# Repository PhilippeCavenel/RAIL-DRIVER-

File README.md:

# RAIL-DRIVER-
 Model railroad board and firmware based on PIC18F4585 

For Board Layout

Important points to remember
---------------------------

Step one: 
----------------

- Generate schematic and validate circuit with ERC
- Pay particular attention to net class, especially for the power section

Second step : 
----------------

- Component placement and automatic routing. 
- To fill in the top and bottom layers, you need to draw a polygon all around the board, selecting the right layer (Top or Bottom) in the top left-hand corner after routing (otherwise it won't work), then restart routing.
- Validate with a DRC, selecting only the Top, Bottom, Via and Pad layers.
- Finalization of the silkscreen (layer 21) by placing all indications correctly and then generating the legend for the drills on layer 144 using drillegend-stack.ulp

Step three: 
-----------------

- Generate the files for manufacturing with the CAM Processor by clicking on the CAM_JOB/RailDriverCamJob.cam file.
- In the top-left File menu, select the .brd file for the corresponding design. 
- The directories and file names must be correct in the various tabs (check and correct if necessary). 
- All that's left to do is to run PROCESS JOB to produce the files.

Fourth step: 
-----------------

- To modify the selection of unknown casings, modify the 3D_RENDERING/eagle3d/ulp/3dusrpac.dat file.  
- Update the configuration files directory in 3dconf.dat 
- Generate a 3D rendering of the design by launching the ULP icon in the layout screen 3D_RENDERING/eagle3d/ulp/3d50.ulp 
- Specify the .brd file, which will generate a .pov file that can be processed by povray to obtain the 3D rendering. 
- Select "User-defined model" in the General tab 
- Add layer 25 in Miscellaneous Case Design
- Modify Writing on plate to display layers 21 and 25 only. 
- Add layers 25 and 27 in Case Reference 
- Click on Create POVRay file and Exit. 
- Copy the generated EAGLE_FILES/RailDriver/RailDriver.pov file into 3D_RENDERING/eagle3d/povray
- Repeat the same operation, moving the camera to shoot from below (using Y) and/or from the other sides (using X and Z).
- Click on the 3D_RENDERING/eagle3d/povray/RailDriver.pov file to start building the 3D view with povray. Use 800 x 600 AA 0.3 for a reasonable image creation time, or 1600 x 1200 A 0.3 for a better resolution, but the image creation time will take several tens of minutes.
- In eagle, make a screen copy of the different layers built during the construction of the manufacturing files. Place all views in PNGVIEW.

HOW TO ADD A 3D MODEL : 
------------------------------

- Retrieve the model in stl format from the Internet (e.g. snapeda). If the model is in step format, it must first be converted to stp, for example on https://polyd.com/fr/convertir-step-en-stl-en-ligne
- Use the stl2pov.exe utility available in utilities (eagle installation directory) (launch a Windows shell) stl2pov.exe myModel.stl > myModel.inc. Copy it to 3D_RENDERING/eagle3d/povray. 

For example: stl2pov.exe "TO220HeatSink\TO220_Heatsink.stp" > "TO220HeatSink\TO220HeatSink.inc".
G
- Modify the myModel.inc file so that it is understood by povray, taking as an example: fk_222_sa.inc
- Add the following include to the 3D_RENDERING/eagle3d/povray/e3d_user.inc file: #include "myModel.inc". 
- Add the following information to the 3D_RENDERING/eagle3d/ulp/3dusrpac.dat file:

Par exemple : FK222:0:1:0:0:0:0:0:0:0:0:0:0:0:0:0:0:0:0:0:0:0:0:0:0:0:0:0:0:0:0:HEATSINK_FK_222(:HEATSINK_FK_222_GRND

Index meaning

[00] Eagle component package name
[01] Output name
[02] Output value
[03] Define color bands
[04] SMD offset (parts will be moved pcb_cuhight up/down)
[05] LED options (The LED options dialog will be displayed)
[06] Ready for sockets (see explanation)
[07] Quartz height request
[08] Has part a macro (for example, SMD jumpers)
[09] SMD resistor, Generate number combination
[10] Socket macro
[11] Height of socket in 1/10mm
[12] Comments concerning socket
[13] Internal for administration purpose (not used at present)
[14] Y axis rotation correction
[15] Correction offset x
[16] Offset correction y
[17] Correction offset z
[18] Use Prefix from Part?
[19] Shunt on pinheader (a dialog will be displayed)
[20] Logo selection dialog will be shown
[21] Reserved[8]
[29] Bounding-Box Minimum
[30] Bounding-Box Maximum
[31] POV-Ray macro (Name of pov macro and a left parenthesis)
[32] Package comments (German)
[33] Package comments (English)

Fifth stage: 
-----------------

- Update the BOM to purchase components

Sixth step:
---------------

-Compress CAM_JOB and PNGVIEW directory to start manufacturing at AllPcb: https://www.allpcb.com/ 

For Firmware : Please read documentation

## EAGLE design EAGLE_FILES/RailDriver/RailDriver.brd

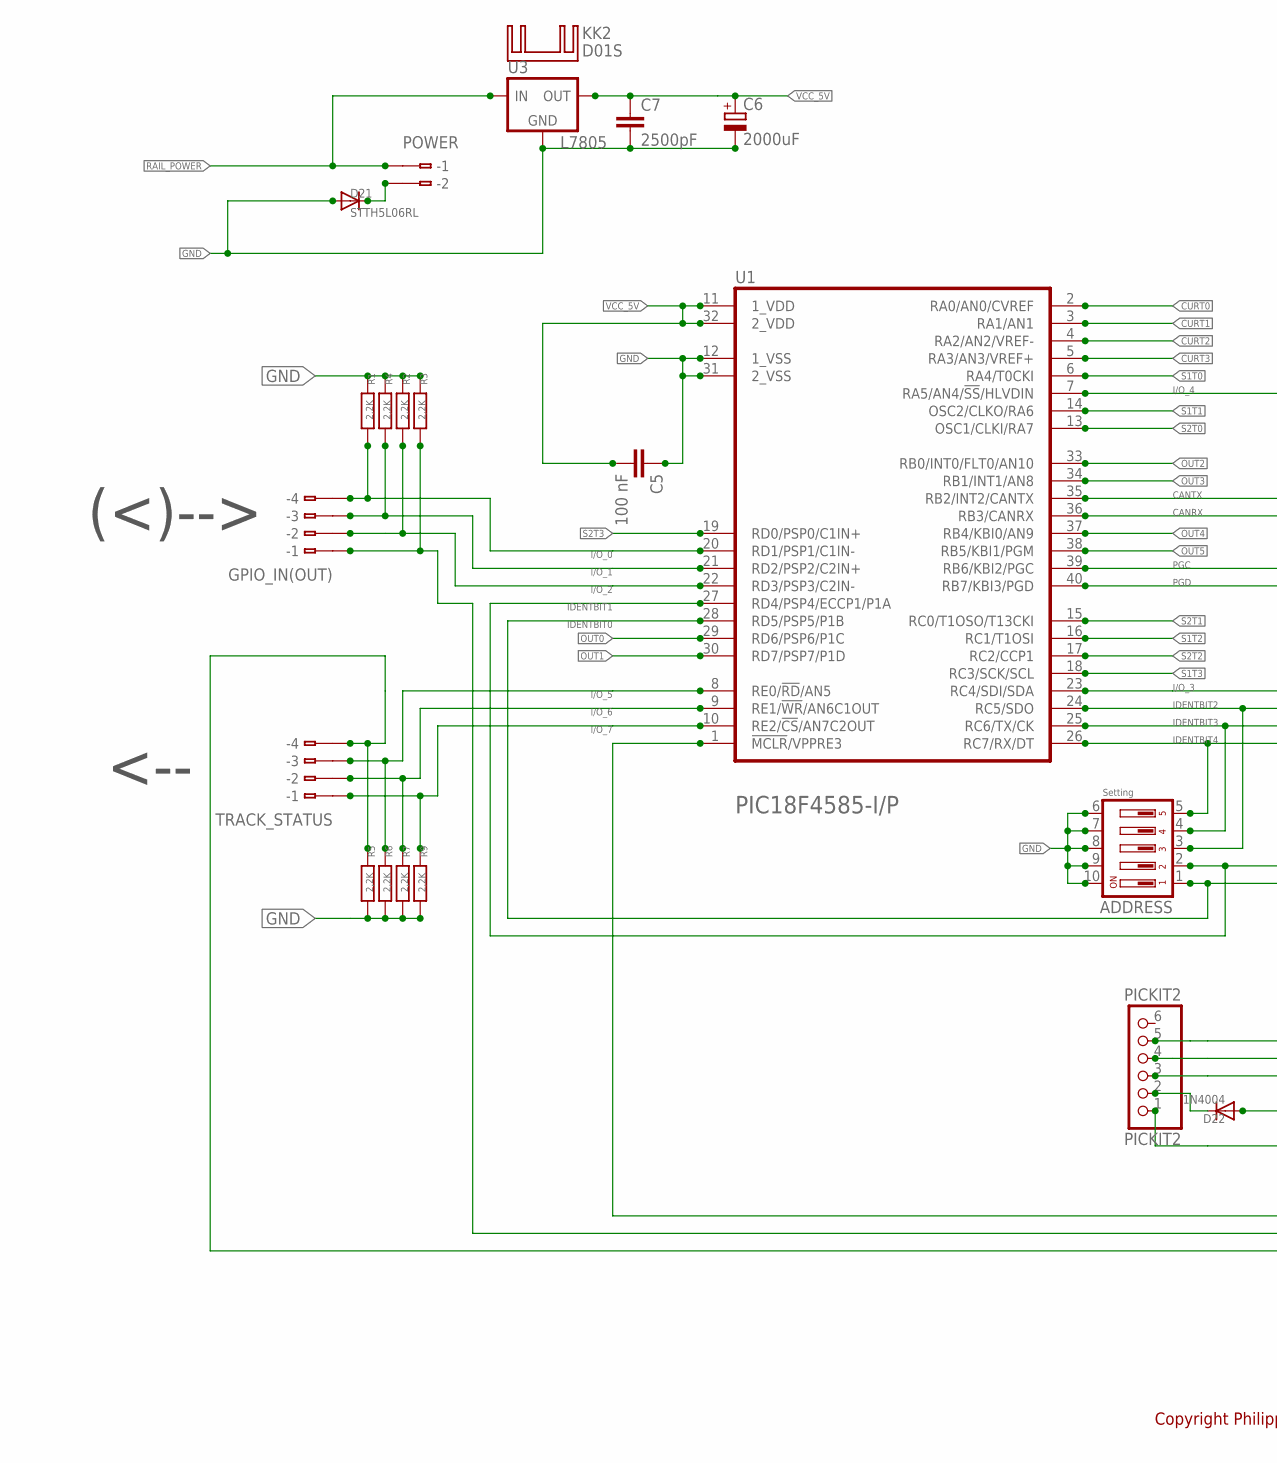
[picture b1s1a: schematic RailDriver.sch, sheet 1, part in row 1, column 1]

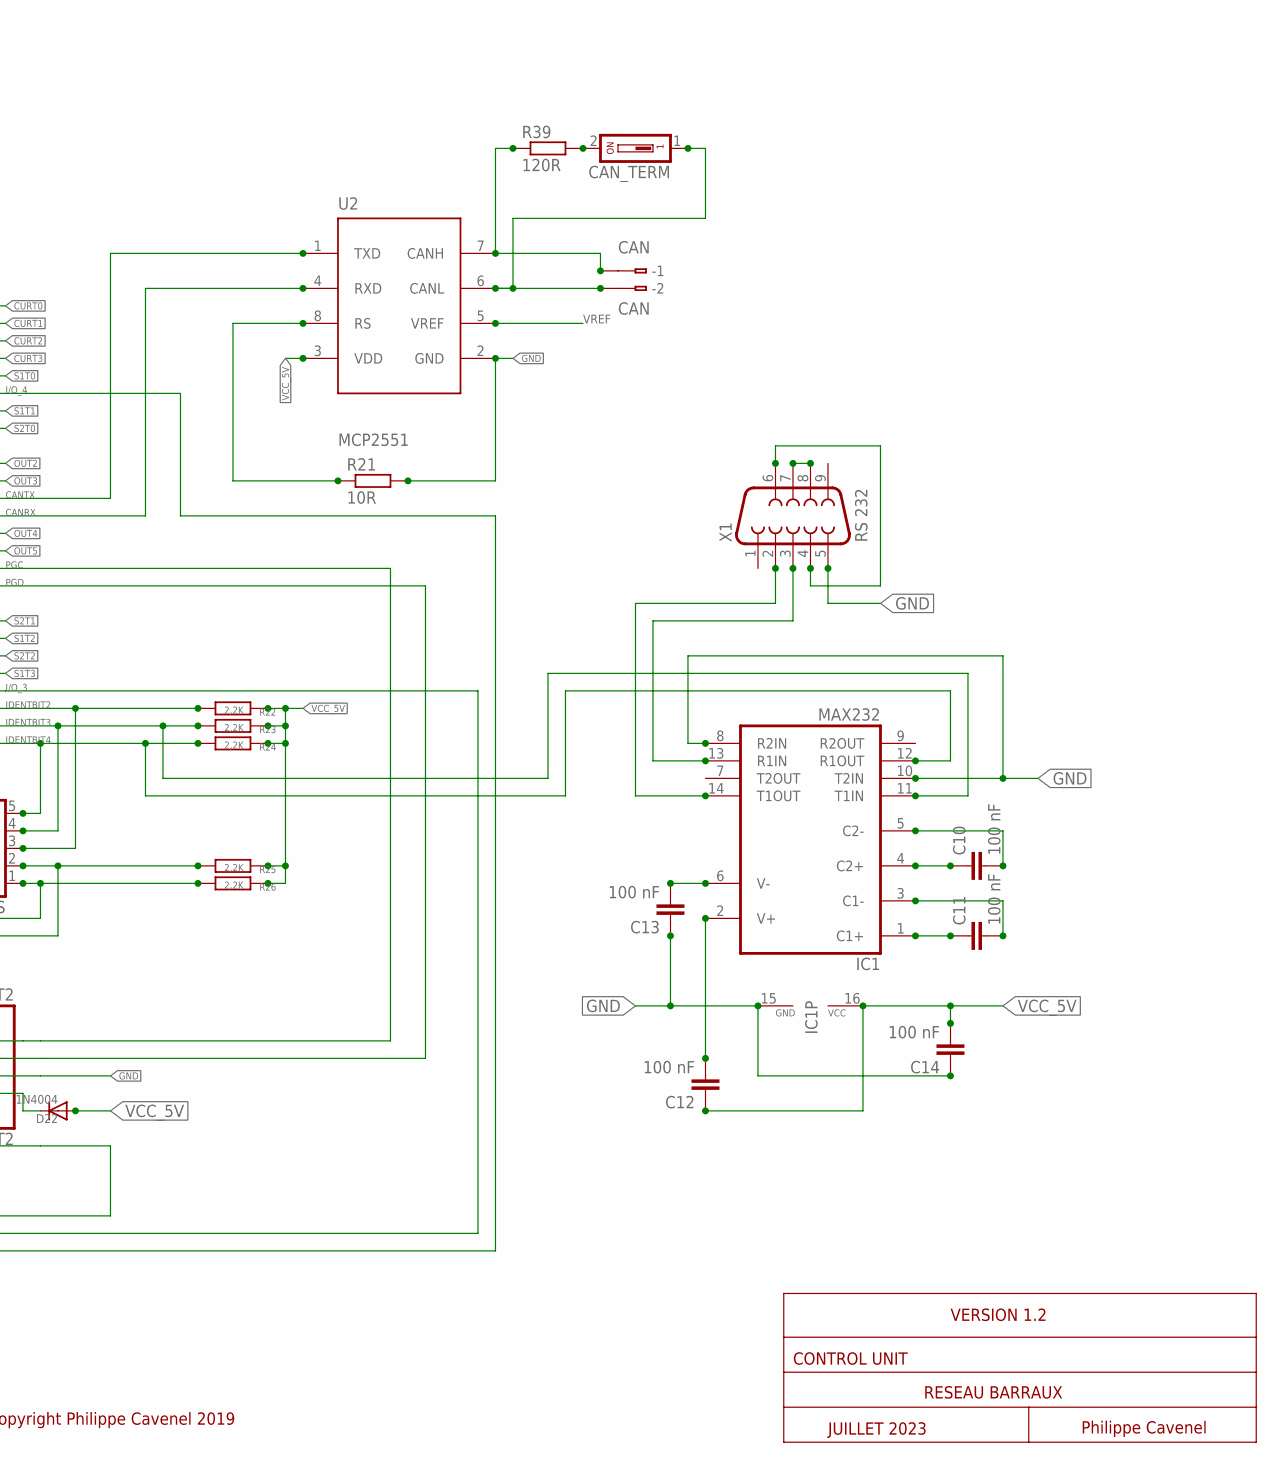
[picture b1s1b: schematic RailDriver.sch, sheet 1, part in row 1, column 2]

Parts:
ADDRESS: DIP05YL
C5, C10, C11, C12, C13, C14: 100 nF; C050-024X044
C6: 2000uF; E3,5-10
C7: 2500pF; C050-024X044
CAN: CAN; 233-502
CAN_TERM: DS01; DS-01
D21: STTH5L06RL; DO201-15
D22: 1N4004; DO41-10
GPIO_IN(OUT): 233-504
IC1: MAX232; DIL16
KK2: D01S
PICKIT2: PICKIT2; 1X06
POWER: 233-502
R1, R2, R3, R4, R5, R6, R7, R9, R22, R23, R24, R25, R26: 2,2K; 0204/7
R21: 10R; 0204/7
R39: 120R; 0204/7
TRACK_STATUS: 233-504
U1: PIC18F4585-I; DIL_SOCKET40W
U2: MCP2551; DIL_SOCKET8
U3: L7805; TO220BV
X1: RS 232; F09HP

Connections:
CANRX: U1.36 (RB3/CANRX), U2.4 (RXD)
CANTX: U1.35 (RB2/INT2/CANTX), U2.1 (TXD)
CURT0: U1.2 (RA0/AN0/CVREF); also elsewhere on the board
CURT1: U1.3 (RA1/AN1); also elsewhere on the board
CURT2: U1.4 (RA2/AN2/VREF-); also elsewhere on the board
CURT3: U1.5 (RA3/AN3/VREF+); also elsewhere on the board
GND: ADDRESS.6, ADDRESS.7, ADDRESS.8, ADDRESS.9, ADDRESS.10, C5.1, C6.-, C7.2, C13.1, C14.1, D21.A, IC1.8 (R2IN), IC1.10 (T2IN), IC1.15 (GND), PICKIT2.3, R1.2, R2.2, R3.2, R4.2, R5.1, R6.1, R7.1, R9.1, R21.2, U1.12 (1_VSS), U1.31 (2_VSS), U2.2 (GND), U3.2 (GND), X1.5; also elsewhere on the board
I/O_0: GPIO_IN(OUT).B4 (B-4), R1.1, U1.20 (RD1/PSP1/C1IN-)
I/O_1: GPIO_IN(OUT).B3 (B-3), R4.1, U1.21 (RD2/PSP2/C2IN+)
I/O_2: GPIO_IN(OUT).B2 (B-2), R2.1, U1.22 (RD3/PSP3/C2IN-)
I/O_3: GPIO_IN(OUT).B1 (B-1), R3.1, U1.23 (RC4/SDI/SDA)
I/O_4: R5.2, TRACK_STATUS.B4 (B-4), U1.7 (RA5/AN4/!SS!/HLVDIN)
I/O_5: R6.2, TRACK_STATUS.B3 (B-3), U1.8 (RE0/!RD!/AN5)
I/O_6: R7.2, TRACK_STATUS.B2 (B-2), U1.9 (RE1/!WR!/AN6C1OUT)
I/O_7: R9.2, TRACK_STATUS.B1 (B-1), U1.10 (RE2/!CS!/AN7C2OUT)
IDENTBIT0: ADDRESS.1, R26.1, U1.28 (RD5/PSP5/P1B)
IDENTBIT1: ADDRESS.2, R25.1, U1.27 (RD4/PSP4/ECCP1/P1A)
IDENTBIT2: ADDRESS.3, R22.1, U1.24 (RC5/SDO)
IDENTBIT3: ADDRESS.4, IC1.11 (T1IN), R23.1, U1.25 (RC6/TX/CK)
IDENTBIT4: ADDRESS.5, IC1.12 (R1OUT), R24.1, U1.26 (RC7/RX/DT)
unnamed: D22.C, PICKIT2.2
unnamed: CAN_TERM.2, R39.2
unnamed: C10.2, IC1.5 (C2-)
unnamed: C10.1, IC1.4 (C2+)
unnamed: C11.1, IC1.1 (C1+)
unnamed: C11.2, IC1.3 (C1-)
unnamed: C12.2, IC1.2 (V+)
unnamed: C13.2, IC1.6 (V-)
unnamed: IC1.13 (R1IN), X1.3
unnamed: IC1.14 (T1OUT), X1.2
unnamed: X1.4, X1.6
unnamed: X1.7, X1.8
unnamed: CAN.B1 (B-1), R39.1, U2.7 (CANH)
unnamed: CAN.B2 (B-2), CAN_TERM.1, U2.6 (CANL)
unnamed: R21.1, U2.8 (RS)
unnamed: D21.C, POWER.B2 (B-2)
unnamed: PICKIT2.1, U1.1 (!MCLR!/VPPRE3)
OUT0: U1.29 (RD6/PSP6/P1C); also elsewhere on the board
OUT1: U1.30 (RD7/PSP7/P1D); also elsewhere on the board
OUT2: U1.33 (RB0/INT0/FLT0/AN10); also elsewhere on the board
OUT3: U1.34 (RB1/INT1/AN8); also elsewhere on the board
OUT4: U1.37 (RB4/KBI0/AN9); also elsewhere on the board
OUT5: U1.38 (RB5/KBI1/PGM); also elsewhere on the board
PGC: PICKIT2.5, U1.39 (RB6/KBI2/PGC)
PGD: PICKIT2.4, U1.40 (RB7/KBI3/PGD)
RAIL_POWER: POWER.B1 (B-1), U3.1 (VIN); also elsewhere on the board
S1T0: U1.6 (RA4/T0CKI); also elsewhere on the board
S1T1: U1.14 (OSC2/CLKO/RA6); also elsewhere on the board
S1T2: U1.16 (RC1/T1OSI); also elsewhere on the board
S1T3: U1.18 (RC3/SCK/SCL); also elsewhere on the board
S2T0: U1.13 (OSC1/CLKI/RA7); also elsewhere on the board
S2T1: U1.15 (RC0/T1OSO/T13CKI); also elsewhere on the board
S2T2: U1.17 (RC2/CCP1); also elsewhere on the board
S2T3: U1.19 (RD0/PSP0/C1IN+); also elsewhere on the board
VCC_5V: C5.2, C6.+, C7.1, C12.1, C14.2, D22.A, IC1.16 (VCC), R22.2, R23.2, R24.2, R25.2, R26.2, U1.11 (1_VDD), U1.32 (2_VDD), U2.3 (VDD), U3.3 (VOUT); also elsewhere on the board
VREF: U2.5 (VREF)

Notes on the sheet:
Philippe Cavenel
RESEAU BARRAUX
CONTROL UNIT
JUILLET 2023
Copyright Philippe Cavenel 2019
Setting
<--
(<)-->
VERSION 1.2

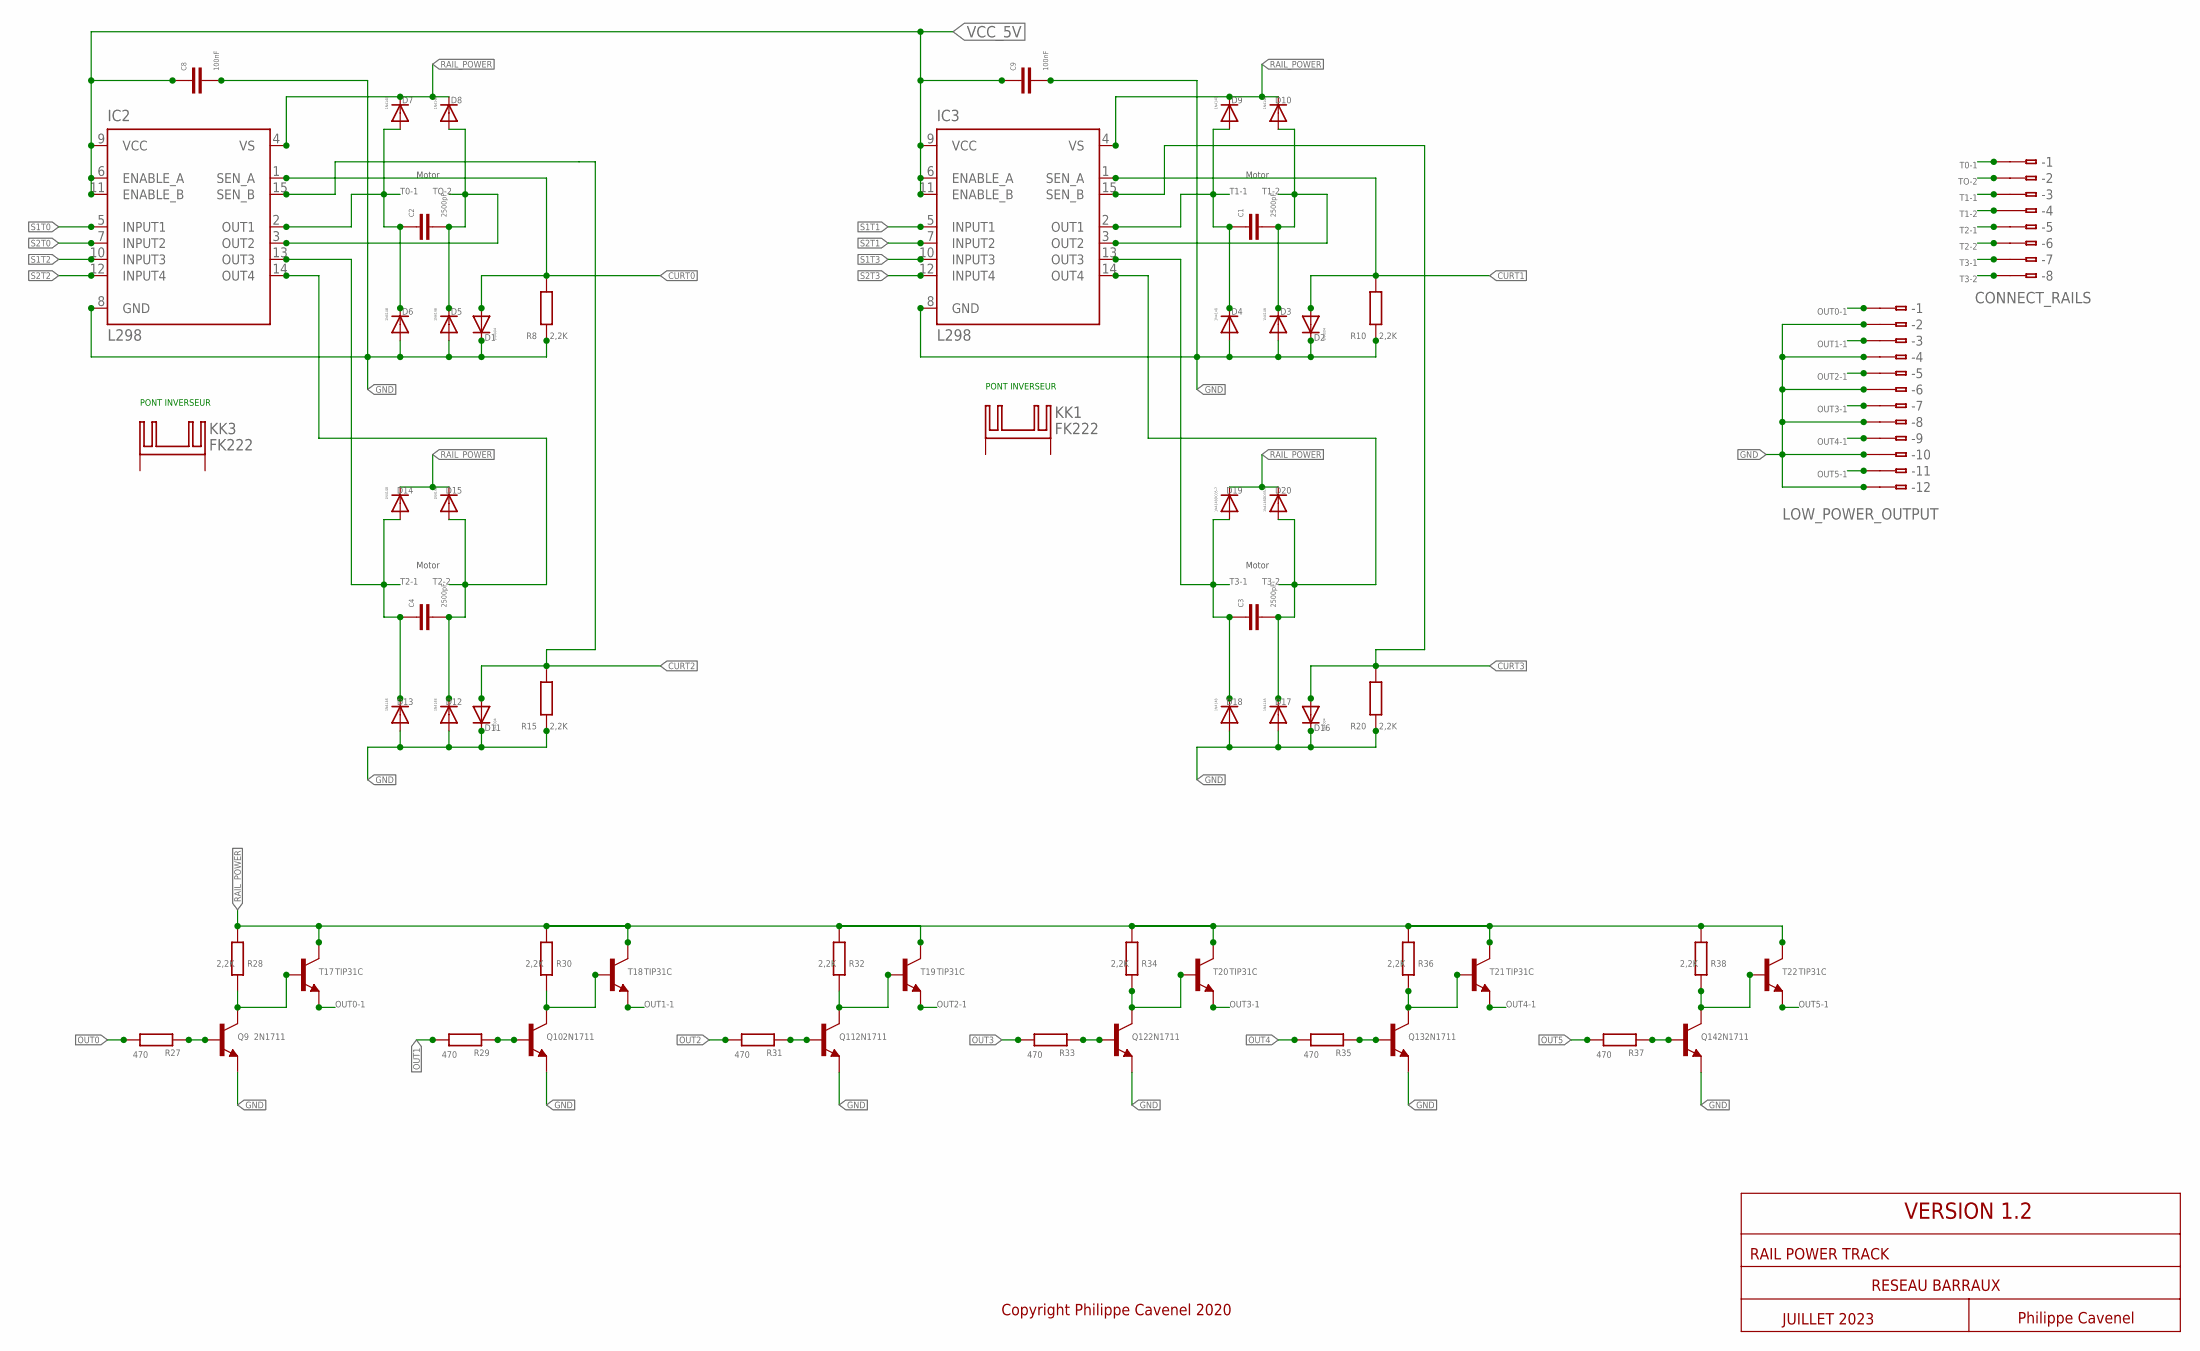
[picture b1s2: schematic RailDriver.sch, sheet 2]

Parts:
C1, C2, C3, C4: 2500pF; C050-024X044
C8, C9: 100nF; C050-024X044
CONNECT_RAILS: 233-508
D1, D2, D11, D16: 1N4004; DO41-10
D3, D4, D5, D6, D7, D8, D9, D10, D12, D13, D14, D15, D17, D18: 1N4148; DO35-7
D19, D20: 1N4148DO35-7; DO35-7
IC2, IC3: L298; MULTIWATT-15
KK1, KK3: FK222
LOW_POWER_OUTPUT: 233-512
Q9, Q10, Q11, Q12, Q13, Q14: 2N1711; TO39
R8, R10, R15, R20, R28, R30, R32, R34, R36, R38: 2,2K; 0204/7
R27, R29, R31, R33, R35, R37: 470; 0204/7
T17, T18, T19, T20, T21, T22: TIP31C; TO220

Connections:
CURT0: D1.A, IC2.1 (SEN_A), R8.2; also elsewhere on the board
CURT1: D2.A, IC3.1 (SEN_A), R10.2; also elsewhere on the board
CURT2: D11.A, IC2.15 (SEN_B), R15.2; also elsewhere on the board
CURT3: D16.A, IC3.15 (SEN_B), R20.2; also elsewhere on the board
GND: C8.2, C9.2, D1.C, D2.C, D3.A, D4.A, D5.A, D6.A, D11.C, D12.A, D13.A, D16.C, D17.A, D18.A, IC2.8 (GND), IC3.8 (GND), LOW_POWER_OUTPUT.B2 (B-2), LOW_POWER_OUTPUT.B4 (B-4), LOW_POWER_OUTPUT.B6 (B-6), LOW_POWER_OUTPUT.B8 (B-8), LOW_POWER_OUTPUT.B10 (B-10), LOW_POWER_OUTPUT.B12 (B-12), Q9.1 (E), Q10.1 (E), Q11.1 (E), Q12.1 (E), Q13.1 (E), Q14.1 (E), R8.1, R10.1, R15.1, R20.1; also elsewhere on the board
unnamed: Q9.3 (C), R28.2, T17.1 (B)
unnamed: Q9.2 (B), R27.1
unnamed: Q10.3 (C), R30.2, T18.1 (B)
unnamed: Q10.2 (B), R29.1
unnamed: Q11.3 (C), R32.2, T19.1 (B)
unnamed: Q11.2 (B), R31.1
unnamed: Q12.3 (C), R34.2, T20.1 (B)
unnamed: Q12.2 (B), R33.1
unnamed: Q13.3 (C), R36.2, T21.1 (B)
unnamed: Q13.2 (B), R35.1
unnamed: Q14.3 (C), R38.2, T22.1 (B)
unnamed: Q14.2 (B), R37.1
OUT0: R27.2; also elsewhere on the board
OUT0-1: LOW_POWER_OUTPUT.B1 (B-1), T17.3 (E)
OUT1: R29.2; also elsewhere on the board
OUT1-1: LOW_POWER_OUTPUT.B3 (B-3), T18.3 (E)
OUT2: R31.2; also elsewhere on the board
OUT2-1: LOW_POWER_OUTPUT.B5 (B-5), T19.3 (E)
OUT3: R33.2; also elsewhere on the board
OUT3-1: LOW_POWER_OUTPUT.B7 (B-7), T20.3 (E)
OUT4: R35.2; also elsewhere on the board
OUT4-1: LOW_POWER_OUTPUT.B9 (B-9), T21.3 (E)
OUT5: R37.2; also elsewhere on the board
OUT5-1: LOW_POWER_OUTPUT.B11 (B-11), T22.3 (E)
RAIL_POWER: D7.C, D8.C, D9.C, D10.C, D14.C, D15.C, D19.C, D20.C, IC2.4 (VS), IC3.4 (VS), R28.1, R30.1, R32.1, R34.1, R36.1, R38.1, T17.2 (C), T18.2 (C), T19.2 (C), T20.2 (C), T21.2 (C), T22.2 (C); also elsewhere on the board
S1T0: IC2.5 (INPUT1); also elsewhere on the board
S1T1: IC3.5 (INPUT1); also elsewhere on the board
S1T2: IC2.10 (INPUT3); also elsewhere on the board
S1T3: IC3.10 (INPUT3); also elsewhere on the board
S2T0: IC2.7 (INPUT2); also elsewhere on the board
S2T1: IC3.7 (INPUT2); also elsewhere on the board
S2T2: IC2.12 (INPUT4); also elsewhere on the board
S2T3: IC3.12 (INPUT4); also elsewhere on the board
T0-1: C2.1, CONNECT_RAILS.B1 (B-1), D6.C, D7.A, IC2.2 (OUT1)
T1-1: C1.1, CONNECT_RAILS.B3 (B-3), D4.C, D9.A, IC3.2 (OUT1)
T1-2: C1.2, CONNECT_RAILS.B4 (B-4), D3.C, D10.A, IC3.3 (OUT2)
T2-1: C4.1, CONNECT_RAILS.B5 (B-5), D13.C, D14.A, IC2.13 (OUT3)
T2-2: C4.2, CONNECT_RAILS.B6 (B-6), D12.C, D15.A, IC2.14 (OUT4)
T3-1: C3.1, CONNECT_RAILS.B7 (B-7), D18.C, D19.A, IC3.13 (OUT3)
T3-2: C3.2, CONNECT_RAILS.B8 (B-8), D17.C, D20.A, IC3.14 (OUT4)
TO-2: C2.2, CONNECT_RAILS.B2 (B-2), D5.C, D8.A, IC2.3 (OUT2)
VCC_5V: C8.1, C9.1, IC2.6 (ENABLE_A), IC2.9 (VCC), IC2.11 (ENABLE_B), IC3.6 (ENABLE_A), IC3.9 (VCC), IC3.11 (ENABLE_B); also elsewhere on the board

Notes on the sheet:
Philippe Cavenel
RESEAU BARRAUX
RAIL POWER TRACK
JUILLET 2023
Copyright Philippe Cavenel 2020
VERSION 1.2
PONT INVERSEUR
Motor

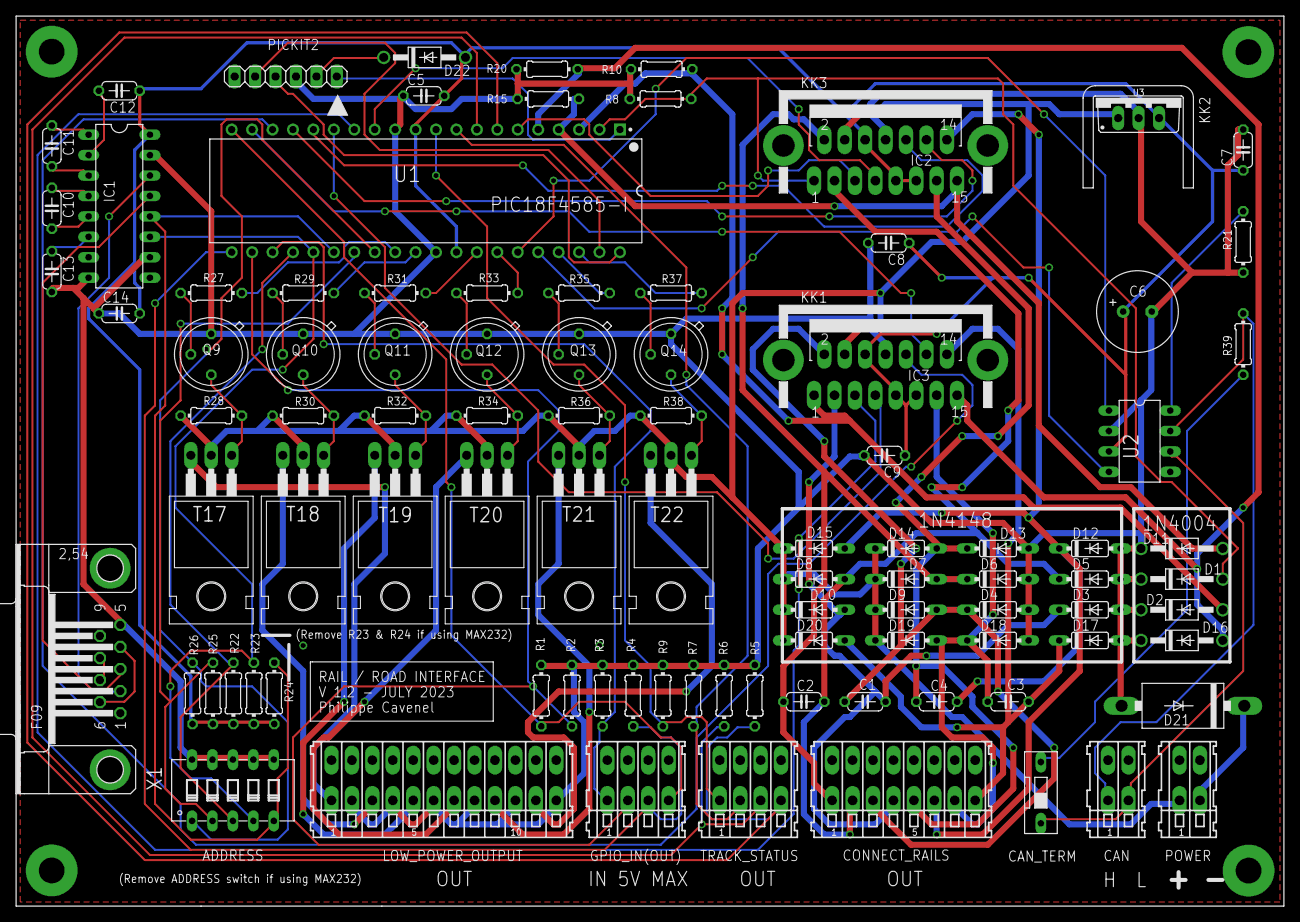
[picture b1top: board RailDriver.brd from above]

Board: 2 copper layers, 157.6 x 110.6 mm, 99 parts (0 on the bottom side), 81 nets.

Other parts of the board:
DRILEGEND: DRILEGEND

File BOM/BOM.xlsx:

| Qty / board | Master only | Dispo | To command | VALUE | DESCRIPTION | Supplier | Ref. | LINK | PRIX UNITAIRE TTC | COUT PROTO | COUT HT
 | 4 |  |  | 4 | Entretoise, Nylon 6.6 (Polyamide 6.6), M3, Hexagonale Mâle-Femelle, 15 mm, 23 mm | Entretoise, Nylon 6.6 (Polyamide 6.6), M3, Hexagonale Mâle-Femelle, 15 mm, 23 mm | FARNELL | 2988235 | https://fr.farnell.com/wurth-elektronik/971150385/entretoise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 | 1.3320000000000001 | 5.3280000000000003 | 4.4400000000000004
 | 0 | YES |  | 0 | Connecteurs D-Sub standards AMPL PLUG HD20, R/A 9P, B/L,4-40 INS | X1 | FARNELL | 2857982 | https://fr.farnell.com/te-connectivity/2301843-1/conn-sub-d-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 | 3.3839999999999999 | 0 | 0
 | 0 | YES |  | 0 | 100nF | C10, C11, C12, C13, C14 | FARNELL | 2309064 | https://fr.farnell.com/kemet/r82dc3100dq50j/cond-0-1-f-63v-5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 | 0.1704 | 0 | 0
 | 3 |  |  | 3 | 100nF | C5 ,C8, C9 | FARNELL | 2309064 | https://fr.farnell.com/kemet/r82dc3100dq50j/cond-0-1-f-63v-5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 | 0.1704 | 0.51119999999999999 | 0.42599999999999999
 | 0 | YES |  | 0 | MAX 232N | IC1 | FARNELL | 3121260 | https://fr.farnell.com/texas-instruments/max232n/ic-transcei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 | 2.2799999999999998 | 0 | 0
 | 1 |  |  | 1 | 2000uF | C6 | FARNELL | 2766923 | https://fr.farnell.com/panasonic-electronic-components/eeufs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 | 0.88639999999999997 | 0.88639999999999997 | 0.73866666666666669
 | 1 |  |  | 1 | 10R | R21 | FARNELL | 2329993 | https://fr.farnell.com/panasonic-electronic-components/eeufs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 | 0.1608 | 0.1608 | 0.13400000000000001
 | 1 |  |  | 1 | 120R | R39 | FARNELL | 2329862 | https://fr.farnell.com/te-connectivity/lr0204f120r/resistanc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 | 0.1368 | 0.1368 | 0.114
 | 16 |  |  | 16 | 1N4148 | D3, D4, D5, D6, D7, D8, D9, D10, D12, D13, D14, D15, D17, D18, D19, D20 | FARNELL | 9843680 | https://fr.farnell.com/on-semiconductor/1n4148tr/diode-tres-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 | 0.13200000000000001 | 2.1120000000000001 | 1.7600000000000002
 | 5 |  |  | 5 | 1N4004 | D22, D1, D11,D2,D16 | FARNELL | 1843708 | https://fr.farnell.com/diodes-inc/1n4004-t/diode-de-redresse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 | 0.252 | 1.26 | 1.05
 | 1 |  |  | 1 | STTH5L06RL | D21 | FARNELL | 2353682 | https://fr.farnell.com/stmicroelectronics/stth5l06rl/diode-r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 | 1.8 | 1.8 | 1.5
 | 23 |  |  | 23 | 2,2K | R1, R2, R3, R4, R5, R6, R7, R8, R9, R10, R15, R20, R22, R23, R24, R25, R26, R28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 | FARNELL | 9341536 | https://fr.farnell.com/multicomp/mf25-2k2/resistance-2-2k-0-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 | 7.4999999999999997E-2 | 1.7249999999999999 | 1.4375
 | 5 |  |  | 5 | 2500pF | C1, C2, C3, C4, C7 | FARNELL | 3289470 | https://fr.farnell.com/vishay/wyo252mcmbrakr/condensateur-su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 | 0.51119999999999999 | 2.556 | 2.1300000000000003
 | 6 |  |  | 6 | 2N1711 | Q9, Q10, Q11, Q12, Q13, Q14 | FARNELL | 1611558 | https://fr.farnell.com/multicomp/2n1711/transistor/dp/161155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 | 2.952 | 17.712 | 14.76
 | 6 |  |  | 6 | 470 | R27, R29, R31, R33, R35, R37 | FARNELL | 9341943 | https://fr.farnell.com/multicomp/mf25-470r/resistance-470r-0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 | 7.8600000000000003E-2 | 0.47160000000000002 | 0.39300000000000002
 | 1 |  |  | 1 | Commutateur DIP / SIP, 5 Circuit(s), Glissière, Traversant, SPST, 24 VDC, 100 mA | ADDRESS | FARNELL | 3397711 | https://fr.farnell.com/alcoswitch-te-connectivity/1825057-4/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 | 1.1988000000000001 | 1.1988000000000001 | 0.99900000000000011
 | 1 |  |  | 1 | Bornier x2 | CAN | FARNELL | 1777096 | https://fr.farnell.com/wago/233-502/bornier-ci-2-54mm-2-voie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 | 1.1856 | 1.1856 | 0.98799999999999999
 | 1 |  |  | 1 | Bornier x2 | POWER | FARNELL | 1777096 | https://fr.farnell.com/wago/233-502/bornier-ci-2-54mm-2-voie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 | 1.1856 | 1.1856 | 0.98799999999999999
 | 1 |  |  | 1 | Commutateur DIP / SIP, 1 Circuit | CAN TERMINATOR | FARNELL | 1960919 | https://fr.farnell.com/omron/a6t1104/commut-dip-raised-actua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 | 1.752 | 1.752 | 1.46
 | 1 |  |  | 1 | Bornier x12 | LOW_POWER_OUTPUT | FARNELL | 1777102 | https://fr.farnell.com/wago/233-512/bornier-ci-2-54mm-12-voi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 | 6.8040000000000003 | 6.8040000000000003 | 5.6700000000000008
 | 1 |  |  | 1 | Bornier x8 | CONNECT_RAILS | FARNELL | 1777101 | https://fr.farnell.com/wago/233-508/bornier-ci-2-54mm-8-voie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 | 4.476 | 4.476 | 3.73
 | 2 |  |  | 2 | Bornier x4 | TRACK_STATUS, GPIO_IN(OUT) | FARNELL | 1777098 | https://fr.farnell.com/wago/233-504/bornier-ci-2-54mm-4-voie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 | 2.8919999999999999 | 5.7839999999999998 | 4.82
 | 1 |  |  | 1 | DollaTek 5Pcs 5V 1A Mini Bloc régulateur à Trois bornes au Lieu de l'entrée LM7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 | U3 | AMAZON |  | https://www.amazon.fr/DollaTek-r%C3%A9gulateur-bornes-lentr%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 | 1.798 | 1.798 | 1.4983333333333335
 | 1 |  |  | 1 | MCP2551P | U2 | FARNELL | 1439745 | https://fr.farnell.com/microchip/mcp2551-e-p/transceiver-can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 | 2.2080000000000002 | 2.2080000000000002 | 1.8400000000000003
 | 1 |  |  | 1 | PIC18F4585-I | U1 | FARNELL | 1439547 | https://fr.farnell.com/microchip/pic18f4585-i-p/mcu-8bit-pic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 | 13.404 | 13.404 | 11.17
 | 1 |  |  | 1 | PICKIT2 | PICKIT2 | FARNELL | 1187827 | Header mâle, Fil à carte, 2.54 mm, 1 Rangée(s), 6 Contact(s), Traversant, droit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 | 2.2080000000000002 | 2.2080000000000002 | 1.8400000000000003
 | 6 |  |  | 6 | TIP31C | T17, T18, T19, T20, T21, T22 | AMAZON |  | https://www.amazon.fr/dp/B08D8VRYN4?psc=1&ref=ppx_yo2ov_dt_b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 | 0.4995 | 2.9969999999999999 | 2.4975000000000001
 | 2 |  |  | 2 | L298N | IC2,IC3 | FARNELL | 403295 | https://fr.farnell.com/stmicroelectronics/l298n/ic-dual-brid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 | 14.58 | 29.16 | 24.3
 | 1 |  |  | 1 | Support CI, 8 Contact(s), Fiche femelle DIP, 2.54 mm, 7.62 mm, Bronze phosphore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 | U2 | FARNELL | 2445620 | https://fr.farnell.com/te-connectivity/1-2199298-2/support-c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 | 0.23039999999999999 | 0.23039999999999999 | 0.192
 | 1 |  |  | 1 | Support CI, 40 Contact(s), Fiche femelle DIP, 2.54 mm, 2227, 15.24 mm, Bronze p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 | U1 | FARNELL | 4285669 | https://fr.farnell.com/multicomp/2227-40-06-05/support-de-ci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 | 0.40560000000000002 | 0.40560000000000002 | 0.33800000000000002
 | 2 |  |  | 2 | FK222 | KK1,KK3 | FARNELL | 1892314 | https://fr.farnell.com/fischer-elektronik/fk-222-sa/heatsink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 | 1.1200000000000001 | 2.2400000000000002 | 1.8666666666666669
 |  |  |  |  |  | Number Board | 2 |  | TOTAL |  | 106.36879999999999 | 88.640666666666661

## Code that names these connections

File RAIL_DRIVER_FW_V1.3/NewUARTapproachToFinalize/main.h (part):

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#define GPIOTHRESHOLD					100

// CIRCUIT 0 ////////////////////////////
#define S1T0							PORTAbits.RA4
#define S2T0    						PORTAbits.RA7
#define CURT0       					0x0 + 0x1 // ADCON0 ON AN0 + ADON

// CIRCUIT 1 ////////////////////////////
#define S1T1							PORTAbits.RA6
#define S2T1    						PORTCbits.RC0
#define CURT1       					0x4 + 0x1 // ADCON0 ON AN1 + ADON

// CIRCUIT 2 ////////////////////////////
#define S1T2							PORTCbits.RC1
#define S2T2    						PORTCbits.RC2
#define CURT2       					0x8 + 0x1 // ADCON0 ON AN2 + ADON

// CIRCUIT 3 ////////////////////////////
#define S1T3							PORTCbits.RC3
#define S2T3    						PORTDbits.RD0
#define CURT3       					0x8 + 0x4 + 0x1 // ADCON0 ON AN3 + ADON

// TRACK STATUS /////////////////////////
#define INKNOB0							0x10 + 0x1 // ADCON0 ON AN4 + ADON	
#define INKNOB1							0x10 + 0x4 + 0x1 // ADCON0 ON AN5 + ADON			
						
// OUTPUT ////////////////////////////
#define OUT0        					PORTDbits.RD6
#define OUT1        					PORTDbits.RD7
#define OUT2        					PORTBbits.RB0
#define OUT3        					PORTBbits.RB1
#define OUT4        					PORTBbits.RB4
#define OUT5        					PORTBbits.RB5

// SWITCH IN ////////////////////////////
#define IN0								PORTCbits.RC5
#define IN1								PORTCbits.RC6
#define IN2								PORTCbits.RC7
#define IN3								PORTDbits.RD4
#define IN4								PORTDbits.RD5

// GPIO IN ///////////////////////////
#define GPIO0							PORTDbits.RD1
#define GPIO1							PORTDbits.RD2
#define GPIO2							PORTDbits.RD3
#define GPIO3							PORTCbits.RC4

///////////////////////////////////////////////
// Token
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
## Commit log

2024-02-06 Improve knobs measurement quality. Add calibration mechanism
2024-02-06 Deleting temporary files
2024-02-22 bug fix
    Correction gestion des trames CAN lors de la mise en route de la carte
2024-04-09 New PIC18F4680 Firmware
    Firmware update for PIC18F4585 + new firmware for PIC18F4680 and companion software to update automation on boards
2025-07-11 update board and Qt editor
    Improve automation for all boards and Qt Editor for a better feedback when data are uploaded
2025-07-12 update board setup & remove old FW
2025-07-14 update cremaillère
2025-07-15 Remove some LPO using relay
2025-07-17 replace all board setup files by BOARD_PROGRAM and add timer reset in automatic mode
2025-07-18 improve firmware stability and boards program
2025-07-20 Added the ability to control multiple tracks simultaneously, speed up data exchange with sribe application
2025-07-20 bugfix on comment line
2025-07-21 bug fix for board calibration and board program improvement
2025-07-25 Start new project for rail manager GUI
2025-07-28 First version of Rail Manager UI available for MacOs & Windows
2025-07-28 Installation tested on the model railway PC
2025-07-28 fix bug on serial port connection
2025-07-28 other bug fix on serial port
2025-07-30 improve GUI & bug fix
2025-07-30 replace run Again button and move it on the scene
2025-07-30 improved board program
2025-07-31 Update main.c
    Restart all after knob calibration
2025-07-31 update documentation
2025-07-31 typo fixed
2025-08-05 Add CAN trace
2025-08-05 remove obj & temp files
2025-08-06 Add color on CAN trace & minor bug fix
2025-08-08 Add Export for trace in RailManagerUI and test code from ChatGPT5 to improveUART
2025-08-10 start to improve can management
2025-08-12 improve CAN management
2025-08-12 Simplify can management to be more robust. Still need to be finalised
2025-08-12 mplab files updated
2025-08-17 improve reliability of CAN
2025-08-18 bug fix on CAN management (CAN_PRINT) and BOARD_PROGRAM update
2025-08-19 add SYNC MANUAL1 MANUAL2 MANUAL3 and improve error feedback for token
2025-08-21 Update speed on one action
2025-08-23 bugfix and improvement
    Add more information on LCD Display, improve reliability of code, add flashing led mode, add watchdog, disable BOR
2025-08-23 bugfix
    disable watchdog during dump and program listing
2025-08-27 remove all warning and messages during compilation
2025-08-27 Improve comments and knobs management + update reference guide
2025-08-27 update reference guide
2025-08-28 remove non existing function in the description
2025-08-29 Change UART speed to 500KBauds
2025-08-29 update information concerning tracks synchronisation
2025-08-29 small fix
2025-08-29 update watchdog value
2025-08-30 Back to 115KBaud, Improve code to get 4 CAN buffer
2025-08-31 bug fix in buffer management
2025-09-06 bugFix & add better follow up of power outage and CAN trame management
2025-09-06 update some speed and timing
2025-09-10 bug fixed in token parsing and add one CAN buffer
2025-09-26 update board program, and remove 1 CAN buffer
2025-09-26 update, add OFFTRACK
2025-09-28 reduce delay before sending CAN trame
2025-09-28 update speed for cars
2025-10-01 Add a mechanism to limit notification on CAN bus
2025-10-03 Bug fixed for the largest frame size
2025-10-22 Add weight
2025-10-22 add offset and arduino code
2025-10-25 improve code stability for poidsMaquette
2025-10-25 small fix to adjust text on poidsMaquette
